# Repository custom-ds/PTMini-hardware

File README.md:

# PTMini Flight Tracker
## * Not under current development *
The PTMini was originally intended to be the second generation APRS tracker from the Project: Traveler group, however it has been tabled for the time being.  Instead the ArduinoTrack Flex is under current development.

[ArduinoTrack Flex Project](https://github.com/custom-ds/ArduinoTrack-Flex-Hardware "ArduinoTrack Flex")

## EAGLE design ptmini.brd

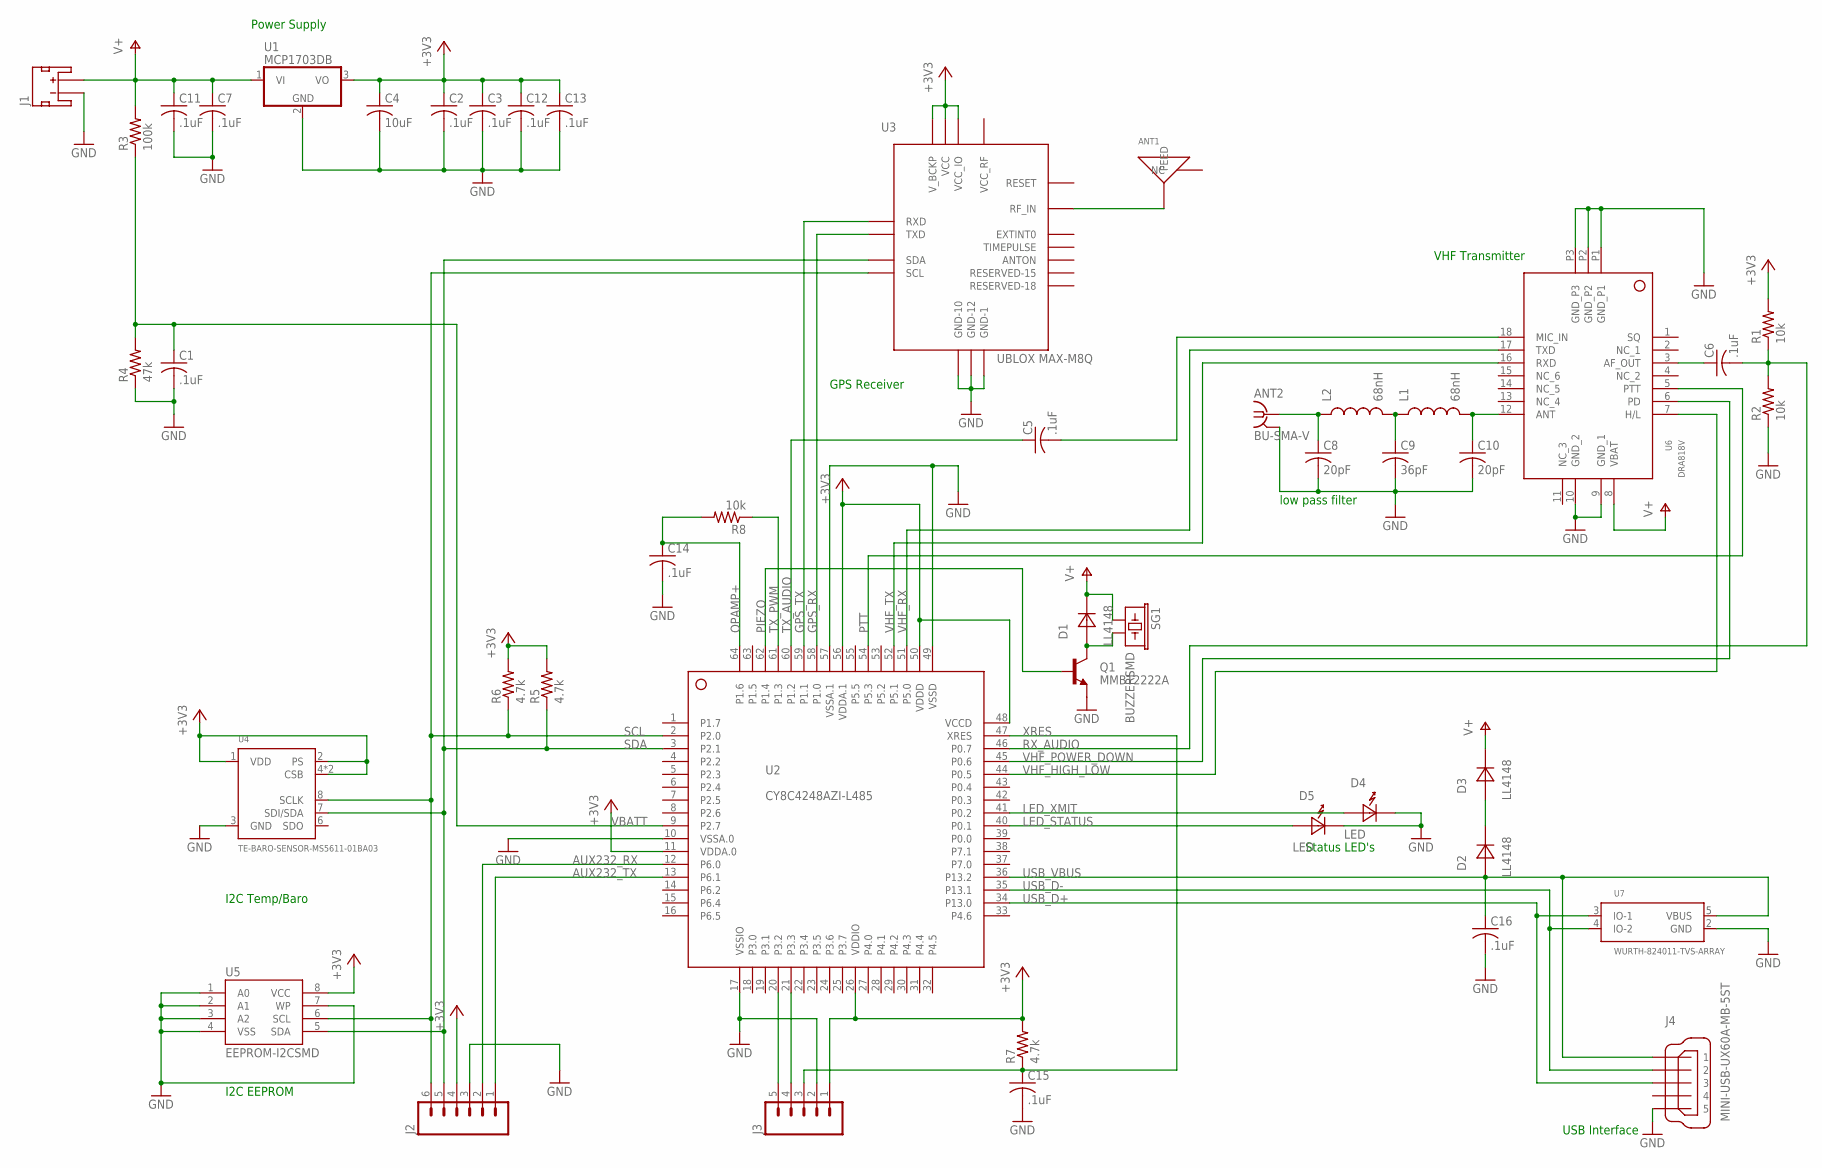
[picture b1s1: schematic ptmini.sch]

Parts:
ANT1: GPS_ANT_SMDBAR; 1575AT43A40; DIGIKEY 712-1003-1-ND
ANT2: BU-SMA-V; DIGIKEY CONSMA001-ND
C1, C2, C3, C5, C6, C7, C11, C12, C13, C14, C15, C16: .1uF; C0805; DIGIKEY 311-1361-1-ND
C4: 10uF; C0805; DIGIKEY 490-3886-1-ND
C8, C10: 20pF; C0805; DIGIKEY 712-1381-1-ND
C9: 36pF; C0805; DIGIKEY 712-1387-1-ND
D1, D2, D3: LL4148; SOD-80; DIGIKEY 568-1749-1-ND
D4: LED; DIODE-1206; DIGIKEY 160-1405-1-ND
D5: LED; DIODE-1206; DIGIKEY 160-1169-1-ND
J1: JST_2MM_MALE; JST-2-SMD; DIGIKEY 455-1749-1-ND
J2: M06RA; MOLEX-1X6-RA; DIGIKEY WM4304-ND
J3: M05LOCK; 1X05_LOCK; DIGIKEY SAM1112-32-ND
J4: MINI-USB-UX60A-MB-5ST; UX60A-MB-5ST; DIGIKEY H2961CT-ND
L1, L2: 68nH; 0805; DIGIKEY AISC-0805-R068G-TCT-ND
Q1: MMBT2222A; SOT23; DIGIKEY MMBT2222AFSCT-ND
R1, R2, R8: 10k; R0805; DIGIKEY 311-10.0KCRCT-ND
R3: 100k; R0805; DIGIKEY 311-100KCRCT-ND
R4: 47k; R0805; DIGIKEY 311-47.0KCRCT-ND
R5, R6, R7: 4.7k; R0805; DIGIKEY 311-4.7KARCT-ND
SG1: BUZZERSMD; BUZZER-CMT1603; DIGIKEY 102-1193-1-ND
U1: MCP1703DB; SOT223; DIGIKEY MCP1703T-3302E/DBCT-ND
U2: CY8C4248AZI-L485; TQFP64-10X10; DIGIKEY 428-3598-ND
U3: UBLOX MAX-M8Q; UBLOX-MAX
U4: TE-BARO-SENSOR-MS5611-01BA03; TE-BARO-SENSOR-MS5611-01BA3; DIGIKEY 223-1622-1-ND
U5: EEPROM-I2CSMD; SO08; DIGIKEY 24LC64F-I/SN-ND
U6: DRA818V; SMD_DRA818
U7: WURTH-824011-TVS-ARRAY; SOT23-5; DIGIKEY 732-4465-1-ND

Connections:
+3V3: C2.1, C3.1, C4.1, C12.1, C13.1, J2.4, J3.1, R1.2, R5.2, R6.2, R7.2, U1.3 (VO), U2.11 (VDDA.0), U2.26 (VDDIO), U2.48 (VCCD), U2.50 (VDDD), U2.56 (VDDA.1), U3.6_V_BCKP (V_BCKP), U3.7_VCC_IO (VCC_IO), U3.8_VCC (VCC), U4.1 (VDD), U4.2 (PS), U4.4 (CSB), U4.5 (CSB), U5.8 (VCC)
AUX232_RX: J2.2, U2.12 (P6.0)
AUX232_TX: J2.1, U2.13 (P6.1)
GND: ANT2.2, ANT2.3 (2), ANT2.4 (2), ANT2.5 (2), C1.2, C2.2, C3.2, C4.2, C7.2, C8.2, C9.2, C10.2, C11.2, C12.2, C13.2, C14.2, C15.2, C16.2, D4.CATHODE, D5.CATHODE, J1.1 (-), J2.3, J3.2, J4.5, Q1.2 (E), R2.1, R4.1, U1.2 (GND), U2.10 (VSSA.0), U2.17 (VSSIO), U2.49 (VSSD), U2.57 (VSSA.1), U3.1_GND (GND-1), U3.10_GND (GND-10), U3.12_GND (GND-12), U4.3 (GND), U5.1 (A0), U5.2 (A1), U5.3 (A2), U5.4 (VSS), U5.7 (WP), U6.9 (GND_1), U6.10 (GND_2), U6.P1 (GND_P1), U6.P2 (GND_P2), U6.P3 (GND_P3), U7.2 (GND)
GPS_RX: U2.58 (P1.0), U3.2_TXD1 (TXD)
GPS_TX: U2.59 (P1.1), U3.3_RXD1 (RXD)
LED_STATUS: D5.ANODE, U2.40 (P0.1)
LED_XMIT: D4.ANODE, U2.41 (P0.2)
unnamed: D1.ANODE, Q1.3 (C), SG1.P$2 (2)
unnamed: C5.2, U6.18 (MIC_IN)
unnamed: ANT1.FEED, U3.11_RF_IN (RF_IN)
unnamed: D2.CATHODE, D3.ANODE
unnamed: C6.1, U6.3 (AF_OUT)
unnamed: ANT2.1, C8.1, L2.1
unnamed: C9.1, L1.1, L2.2
unnamed: C10.1, L1.2, U6.12 (ANT)
unnamed: J3.5, U2.20 (P3.2)
unnamed: J3.4, U2.21 (P3.3)
OPAMP+: C14.1, R8.2, U2.64 (P1.6)
PIEZO: Q1.1 (B), U2.62 (P1.4)
PTT: U2.54 (P5.3), U6.5 (PTT)
RESET: U3.9_V_RESET (RESET)
RX_AUDIO: C6.2, R1.1, R2.2, U2.46 (P0.7)
SCL: J2.6, R6.1, U2.2 (P2.0), U3.17_SCL2 (SCL), U4.8 (SCLK), U5.6 (SCL)
SDA: J2.5, R5.1, U2.3 (P2.1), U3.16_SDA2 (SDA), U4.7 (SDI/SDA), U5.5 (SDA)
TX_AUDIO: C5.1, U2.60 (P1.2)
TX_PWM: R8.1, U2.61 (P1.3)
USB_D+: J4.3, U2.34 (P13.0), U7.3 (IO-1)
USB_D-: J4.2, U2.35 (P13.1), U7.4 (IO-2)
USB_VBUS: C16.1, D2.ANODE, J4.1, U2.36 (P13.2), U7.5 (VBUS)
V+: C7.1, C11.1, D1.CATHODE, D3.CATHODE, J1.2 (+), R3.2, SG1.P$1 (1), U1.1 (VI), U6.8 (VBAT)
VBATT: C1.1, R3.1, R4.2, U2.9 (P2.7)
VHF_HIGH_LOW: U2.44 (P0.5), U6.7 (H/L)
VHF_POWER_DOWN: U2.45 (P0.6), U6.6 (PD)
VHF_RX: U2.51 (P5.0), U6.17 (TXD)
VHF_TX: U2.52 (P5.1), U6.16 (RXD)
XRES: C15.1, J3.3, R7.1, U2.47 (XRES)

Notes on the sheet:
low pass filter
Status LED's
USB Interface
VHF Transmitter
GPS Receiver
Power Supply
I2C Temp/Baro
I2C EEPROM

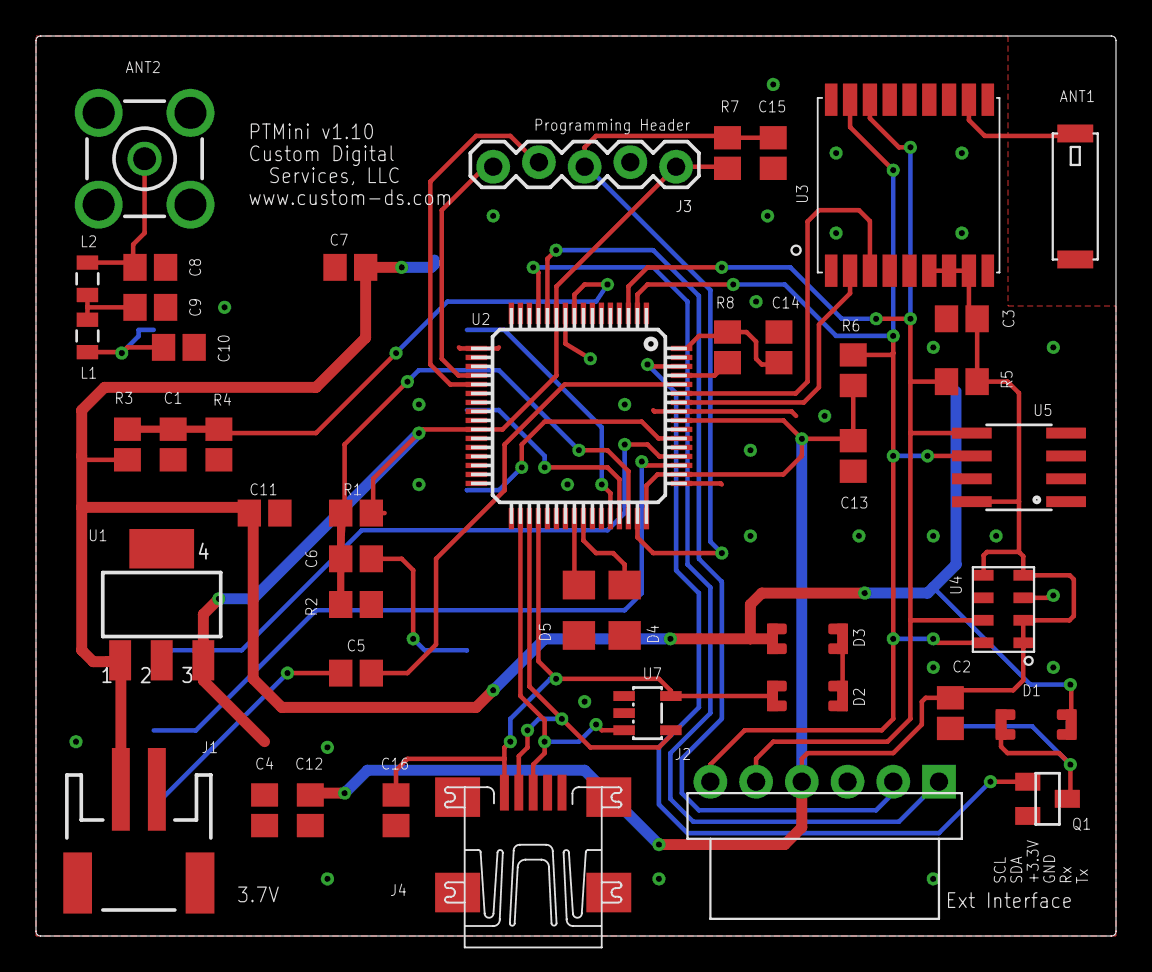
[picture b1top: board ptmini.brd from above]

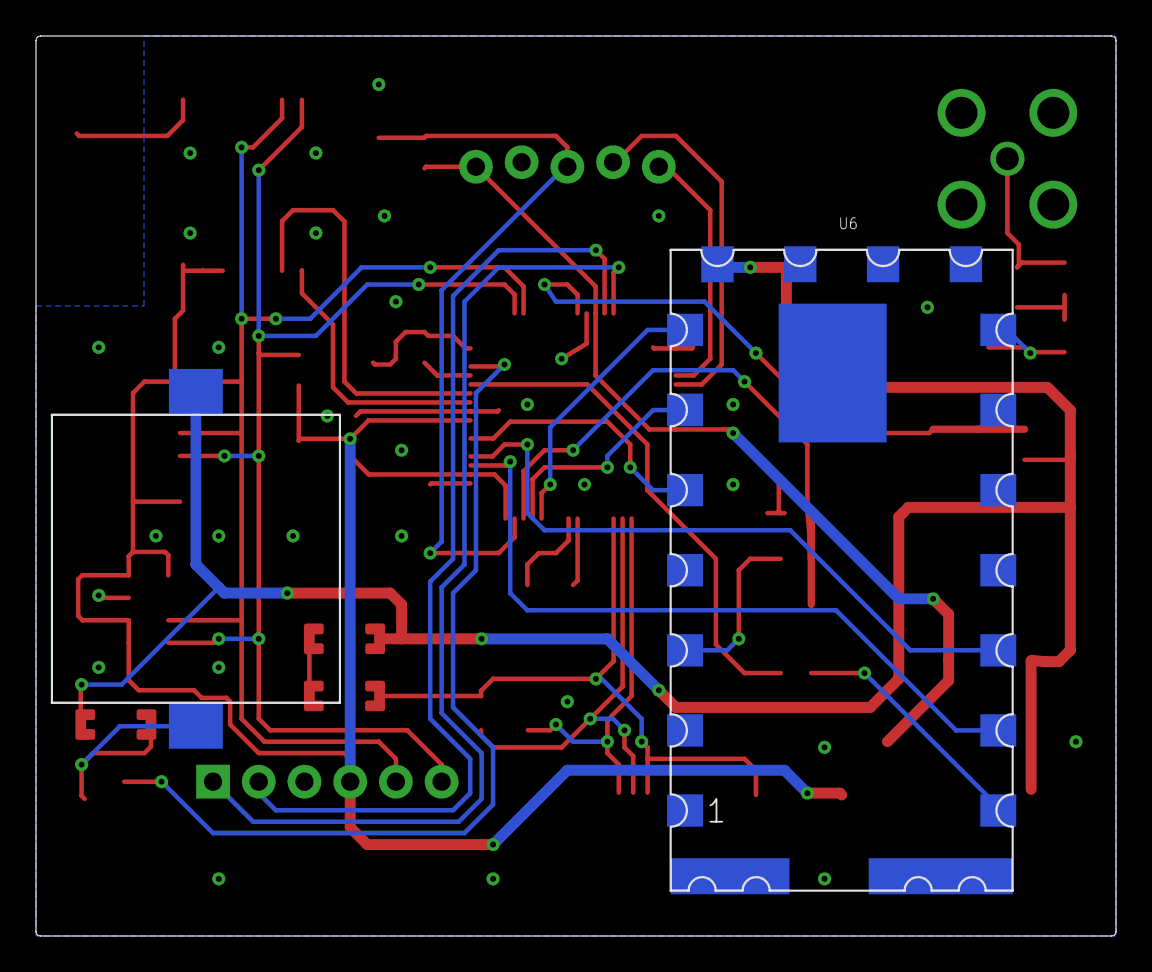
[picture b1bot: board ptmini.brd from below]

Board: 2 copper layers, 60.0 x 50.0 mm, 46 parts (2 on the bottom side), 36 nets.

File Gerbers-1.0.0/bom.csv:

"Part";"Value";"Device";"Package";"Description";"DIGIKEY";"MF";"MPN";"OC_FARNELL";"OC_NEWARK";"PROD_ID";"VALUE";
"ANT1";"GPS_ANT_SMDBAR";"GPS_ANT_SMDBAR";"1575AT43A40";"1.575 GHz GPS Antenna Johanson Technology";"712-1003-1-ND";"";"";"";"";"";"";
"ANT2";"BU-SMA-V";"BU-SMA-V";"BU-SMA-V";"FEMALE SMA CONNECTOR";"CONSMA001-ND";"";"";"unknown";"unknown";"";"";
"C1";".1uF";"C-USC0805";"C0805";"CAPACITOR, American symbol";"311-1361-1-ND";"";"";"";"";"";"";
"C2";".1uF";"C-USC0805";"C0805";"CAPACITOR, American symbol";"311-1361-1-ND";"";"";"";"";"";"";
"C3";".1uF";"C-USC0805";"C0805";"CAPACITOR, American symbol";"311-1361-1-ND";"";"";"";"";"";"";
"C4";".1uF";"C-USC0805";"C0805";"CAPACITOR, American symbol";"311-1361-1-ND";"";"";"";"";"";"";
"C5";".1uF";"C-USC0805";"C0805";"CAPACITOR, American symbol";"311-1361-1-ND";"";"";"";"";"";"";
"C6";".1uF";"C-USC0805";"C0805";"CAPACITOR, American symbol";"311-1361-1-ND";"";"";"";"";"";"";
"C7";".1uF";"C-USC0805";"C0805";"CAPACITOR, American symbol";"311-1361-1-ND";"";"";"";"";"";"";
"C8";"20pF";"C-USC0805";"C0805";"CAPACITOR, American symbol";"712-1381-1-ND";"";"";"";"";"";"";
"C9";"36pF";"C-USC0805";"C0805";"CAPACITOR, American symbol";"712-1387-1-ND";"";"";"";"";"";"";
"C10";"20pF";"C-USC0805";"C0805";"CAPACITOR, American symbol";"712-1381-1-ND";"";"";"";"";"";"";
"C11";"47uF";"CPOL-US153CLV-0605";"153CLV-0605";"POLARIZED CAPACITOR, American symbol";"PCE3842CT-ND";"";"";"";"";"";"";
"C12";".1uF";"C-USC0805";"C0805";"CAPACITOR, American symbol";"311-1361-1-ND";"";"";"";"";"";"";
"C13";".1uF";"C-USC0805";"C0805";"CAPACITOR, American symbol";"311-1361-1-ND";"";"";"";"";"";"";
"C14";".1uF";"C-USC0805";"C0805";"CAPACITOR, American symbol";"311-1361-1-ND";"";"";"";"";"";"";
"C15";".1uF";"C-USC0805";"C0805";"CAPACITOR, American symbol";"311-1361-1-ND";"";"";"";"";"";"";
"C16";".1uF";"C-USC0805";"C0805";"CAPACITOR, American symbol";"311-1361-1-ND";"";"";"";"";"";"";
"C17";".1uF";"C-USC0805";"C0805";"CAPACITOR, American symbol";"311-1361-1-ND";"";"";"";"";"";"";
"D1";"LL4148";"LL4148";"SOD-80";"General purpose LL1448 Diode in the SOD-80 (glass tube) form factor.";"568-1749-1-ND";"";"";"";"";"";"";
"D2";"LL4148";"LL4148";"SOD-80";"General purpose LL1448 Diode in the SOD-80 (glass tube) form factor.";"568-1749-1-ND";"";"";"";"";"";"";
"D3";"LL4148";"LL4148";"SOD-80";"General purpose LL1448 Diode in the SOD-80 (glass tube) form factor.";"568-1749-1-ND";"";"";"";"";"";"";
"D4";"LED";"LED";"DIODE-1206";"Light Emitting Diode (LED) in a 1206 SMT package.";"160-1405-1-ND";"";"";"";"";"";"";
"D5";"LED";"LED";"DIODE-1206";"Light Emitting Diode (LED) in a 1206 SMT package.";"160-1169-1-ND";"";"";"";"";"";"";
"J1";"";"JST_2MM_MALE";"JST-2-SMD";"Mates to single-cell LiPo batteries.";"455-1749-1-ND";"";"";"";"";"CONN-08352";"";
"J2";"";"M06RA";"MOLEX-1X6-RA";"Header 6";"WM4304-ND";"";"";"";"";"";"";
"J3";"";"M05LOCK";"1X05_LOCK";"Header 5";"SAM1112-32-ND";"";"";"";"";"";"";
"J4";"MINI-USB-UX60A-MB-5ST";"MINI-USB-UX60A-MB-5ST";"UX60A-MB-5ST";"MINI USB Connector";"H2961CT-ND";"";"";"unknown";"unknown";"";"";
"L1";"68nH";"INDUCTOR0805";"0805";"Inductors";"535-11572-2-ND OR AISC-0805-R068G-TCT-ND";"";"";"";"";"";"";
"L2";"68nH";"INDUCTOR0805";"0805";"Inductors";"535-11572-2-ND OR AISC-0805-R068G-TCT-ND";"";"";"";"";"";"";
"Q1";"MMBT2222A";"TRANSISTOR_NPNMMBT2222A";"SOT23";"Generic NPN BJT";"MMBT2222AFSCT-ND";"";"";"";"";"TRANS-08049";"MMBT2222A";
"R1";"10k";"R-US_R0805";"R0805";"RESISTOR, American symbol";"311-10.0KCRCT-ND";"";"";"";"";"";"";
"R2";"10k";"R-US_R0805";"R0805";"RESISTOR, American symbol";"311-10.0KCRCT-ND";"";"";"";"";"";"";
"R3";"100k";"R-US_R0805";"R0805";"RESISTOR, American symbol";"311-100KCRCT-ND";"";"";"";"";"";"";
"R4";"47k";"R-US_R0805";"R0805";"RESISTOR, American symbol";"311-47.0KCRCT-ND";"";"";"";"";"";"";
"R5";"4.7k";"R-US_R0805";"R0805";"RESISTOR, American symbol";"311-4.7KARCT-ND";"";"";"";"";"";"";
"R6";"4.7k";"R-US_R0805";"R0805";"RESISTOR, American symbol";"311-4.7KARCT-ND";"";"";"";"";"";"";
"R7";"4.7k";"R-US_R0805";"R0805";"RESISTOR, American symbol";"311-4.7KARCT-ND";"";"";"";"";"";"";
"R8";"10k";"R-US_R0805";"R0805";"RESISTOR, American symbol";"311-10.0KCRCT-ND";"";"";"";"";"";"";
"SG1";"BUZZERSMD";"BUZZERSMD";"BUZZER-CMT1603";"Buzzer 12mm";"102-1193-1-ND";"";"";"";"";"";"";
"U1";"MCP1703DB";"MCP1703DB";"SOT223";"250 mA, 16V, Low Quiescent Current LDO Regulator";"MCP1703T-3302E/DBCT-ND";"";"";"";"";"";"";
"U2";"CY8C4248AZI-L485";"CY8C4248AZI-L485";"QFP64_SOT393";"";"428-3598-ND";"";"";"";"";"";"";
"U3";"UBLOX-MAX";"UBLOX-MAX";"UBLOX-MAX";"UBlox MAX-series of GPS receiver engines.";"";"";"";"";"";"";"";
"U4";"MS5611-01BA03";"MS5611-01BA03";"MS5611-01BA03";"MS5611-01BA03 Barometric Pressure Sensor";"223-1622-1-ND";"";"";"";"";"";"";
"U5";"EEPROM-I2CSMD";"EEPROM-I2CSMD";"SO08";"I2C EEPROM chips, 24LC256 (and others)";"24LC64F-I/SN-ND";"";"";"";"";"";"";
"U6";"DRA818V";"DRA818V";"SMD_DRA818";"DRA818V is a compact wireless voice transceiver from Dorji.";"";"";"";"";"";"";"";
"U7";"PUSBM12VX4-TL-115";"PUSBM12VX4-TL-115";"PUSBM12VX4-TL-115";"";"568-10918-1-ND";"";"";"";"";"";"";

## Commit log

2016-07-15 Board version 1.00
    First run at the PTMini PCB. Placed the VHF model on the back of the
    board. Most of the Digikey part numbers are keyed in, but a few are
    still outstanding.
2016-07-17 Board version 1.01.
    Minor changes to a few of the component libraries. Swapped out the
    diodes with a smaller LL4148 diode. Defined all component values and
    Digikey part numbers. Set values for low pass filter. Renumbered board
    to 1.01 to reflect the slight layout changes. All components remain
    unchanged otherwise.
2016-07-29 Board version 1.1.0
    Fixed incorrect chip footprint for PSoC chip, and also a bad power
    connection to the chip. Relocated the piezo to the back side of the PCB
    and consolidated down to 5cm x 6cm.
2018-12-28 Updating readme with not under development

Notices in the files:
parts and their libraries:
SparkFun-Electromechanical: Licensing: CC v3.0 Share-Alike You are welcome to use this library for commercial purposes.
